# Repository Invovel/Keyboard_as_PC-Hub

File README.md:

# Keyboard as PC Hub

**Desktop Control Hub · R3.1：Core＋可选下置Power Dock＋低功耗MAG附件。**

Core背部PC-C是唯一电脑上行，单线从电脑允许的VBUS预算取电，目标为不依赖Dock即可使用主体与键盘。Hub硬件转发USB外设数据，ESP32负责圆屏、旋钮、四键、音频和HID；Hub启动不应依赖ESP32固件。单线功耗、Hub配置与故障独立性尚未通过整机验证。

[最新交接基准](docs/R3_1_CODEX_HANDOFF.md) · [差异与决策台账](docs/R3_1_DECISIONS.md) · [WP1/WP2工程评审](docs/R3_1_ENGINEERING_REVIEW.md) · [下一步入口](CODEX_START.md)

[补充讨论采用/放弃清单](docs/R3_1_SUPPLEMENT.md)：保留五键与104mm前部横条，补强Hub启动和Slider验证，早期双向供电/竖条/第二上行不混入当前设计。

**新增设计决定：[最右侧 ISO／DEBUG USB-A](docs/iso-debug-r3-1.md)。** PC-C候选中心移至X≈+64，ISO口X≈+91；由P6经独立USB2双下游Hub保留CTRL并增设隔离调试链路。首版采用隔离电源、集成限流/短路/防反灌保护、数据ESD和本地故障指示；精确计量留作后续选装。[候选材料表](hardware/electronics/iso-debug-candidate-bom.csv)不等于采购或保护能力认证。

[原理图摆位表](docs/iso-debug-schematic-placement-r3-1.md) · [A3摆位视图](design/drawings/iso-debug-schematic-placement-r3-1.svg) · [首版功能连接参考](design/drawings/iso-debug-minimal-schematic-r3-1.svg) · [Anatomy结构视图](design/visualization/iso-debug-anatomy.html) · [预览图](design/visualization/iso-debug-anatomy-preview.png)。当前仅确定原理图页内位置，未画导线或PCB；现有KiCad主工程尚未写入该页。

## 当前结构与接口

| 部位 | R3.1分工 |
| --- | --- |
| Core背部 | A1、A2、PC-C、最右侧ISO／DEBUG USB-A；PC-C唯一电脑上行，无Core POWER输入 |
| Core左侧 | FAST-C，目标10Gbps下游；实际供电按预算，不预先承诺3A |
| KBD / CTRL | 可调Type-C键盘公头 / 内部ESP32 USB2 Full-Speed HID |
| Core底部 | P4 Dock DATA＋独立PWR/CTRL预留，封装与开孔未定 |
| 可选下置Dock | Rev B：扩展Hub、外部PD受电、保护降压、单向给Core供电；没有第二电脑上行 |
| 两端MAG | 低速、低功耗8触点；五键及前部唯一横向触控条，不传高速USB/全机电流 |

逻辑下游P1=A1、P2=A2、P3=FAST、P4=DOCK、P5=KBD、P6=USB2分支至原CTRL与新ISO／DEBUG；这是架构分配，不是芯片物理引脚。USB7206C仍为候选，尚未证明Core单线工作能力。旧A3迁为Dock数据链路，POWER IN移至Dock；旧100W/46W单体预算仅保留为历史。

| 尺寸 | 候选值，mm |
| --- | --- |
| Core / PCB | 228×76、5°，前20/后26.65；PCB216×64×1.6 |
| 短四键 | 四片镜像，外端X=±84，两端各留30固定壳面；键面高0.3 |
| 感应中心 | (±65,±18)，保持原位 |
| 环 / 屏 / AA | Ø60 / Ø44.32 / Ø38.16；单边可见边框1.8 |
| 五键 / 横条 | 112×76一字五键；前部横条104×22×8，目标有效长90～96 |
| 底部Dock研究区 | 48×18功能区；8板间距和20高Dock包络均未冻结 |

新增[左右马达预留与PCB布局](hardware/pcb/references/core-haptic-placement-r3-1.md)：2026-10-22锁定[iPhone 7 Plus Taptic Engine](docs/haptic-iphone-7-plus.md)，按用户给定含耳50×12.5×2.6 mm设计，每侧装配区改为15×54×6 mm、长边沿Y，两端顶面保持完整留白。接线采用六测试焊盘最外侧两点接独立触觉驱动；[本轮原生执行记录](hardware/pcb/references/haptic-7plus-native-update.md)与[10月19日历史板图/DRC](hardware/pcb/exports/core-r3-1-haptic-study/README.md)分开保存。新板尚未接网/布线，不能打样。

## 原HTML持续更新

[原单文件HTML](design/visualization/hairline-keyboard-hub.html) · [使用与截图](design/visualization/README.md)。下载后离线打开；悬停主体展开、点击固定/复位，右侧五键及横条磁吸拆分。可选Dock只在主体展开时显示研究包络；默认Core不装Dock。GitHub README仅显示静态图。

[底部接口与侧剖](design/drawings/dock-interface-r3-1.svg) · [R3.1机械说明](hardware/enclosure/dimensions-r3-1.md) · [端口选型表](hardware/electronics/dock-port-selection.csv)

[ISO口与右马达、后孔空间关系](design/drawings/iso-debug-rear-study-r3-1.svg)：这是候选二维研究，开孔仍未冻结。

## 实物进展与文件分类

已运行主体：圆屏、触控页面、触摸板、USB键鼠/媒体HID、四键、按压输入、编码器与提示音；[实测历史](docs/body-core-bringup.md)保留原文。Touchpad延迟本轮不改。新增[INMP441代码](docs/microphone-inmp441.md)只编译，默认关闭，未接实物。输入按压通过不代表屏幕Z轴机械机构已完成。

| 分类 | 入口 | 状态 |
| --- | --- | --- |
| 固件 | [firmware](firmware/README.md) | 保留已运行GPIO与整合代码，本轮不改动/烧录 |
| 展示与图纸 | [design](design/README.md) | 原HTML、R3.1俯视/底视/剖面示意 |
| 机械 | [hardware/enclosure](hardware/enclosure/README.md) | R3.1参数/草模，未实体编译与装配验证 |
| PCB | [hardware/pcb](hardware/pcb/README.md) | 新增指定工程的R3.1布局草案与马达预留；未接网/布线，DRC未通过；R3载板保留历史 |
| 接口与接线 | [hardware/electronics](hardware/electronics/README.md) | 新接口目标与既有实物分开记录 |
| 镜像与证据 | [releases](releases/README.md)、[tests](tests/README.md) | 保留原镜像、许可和真实日志 |

尚未完成电源/Hub/Dock电路、连接器冻结、ERC、USB合规、闭壳温升或制造放行。新增布局已运行DRC但未通过；完整原理图与电气连接仍待完成。不做第二上行、双向大电流、手机高压PD输出、读卡、电池或竖触控条。

[目录规则](docs/repository-layout.md) · [本轮检查](tests/design/r3-1-review.md) · [R3历史尺寸](hardware/enclosure/dimensions-r3.md) · [旧单体供电方案](docs/desktop-power-dock.md) · [R2历史](hardware/enclosure/dimensions-r2.md)

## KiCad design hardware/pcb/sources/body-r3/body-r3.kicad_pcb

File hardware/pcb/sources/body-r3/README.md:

# R3 模块接口载板草稿

> 本工程保留为历史被动接口载板。本轮没有修改KiCad文件；R3.1原生Core与Dock电气仍待设计，见[最新审查](../../../../docs/R3_1_ENGINEERING_REVIEW.md)。下文100W单体供电及旧生成器说明不代表当前Core结构；不要运行旧生成器覆盖新版参数/图纸，KiCad后续修改须通过Konnect。

这是基于当前已运行固件 GPIO 与模块拓扑生成的 **KiCad 接口原理图 + PCB 布局草稿**。不是 Keychron PCB 的复刻，也不是制造放行板。

按[桌面供电底座定位](../../../../docs/desktop-power-dock.md)，本板是控制载板。新增100W等级PD输入、5V分路供电与USB7206C Hub需要单独子板，**本板J9仍只接5V**；更新产品定位没有实现这些电源电路。

- [body-r3.kicad_pro](body-r3.kicad_pro)：项目入口。
- [body-r3.kicad_sch](body-r3.kicad_sch)：内嵌连接器符号的原理图，11 个逻辑接口。
- [body-r3.kicad_pcb](body-r3.kicad_pcb)：216×64×1.6 mm 板框、34 个网络（包含空网络编号 0）、15 个封装（含安装孔）。**没有走线与铺铜**。
- [generate.py](generate.py)：已停用的旧入口，返回非零且不写文件；[原生成源文本](generate-r3-legacy.py.txt)只供历史阅读。新机械/参数用[update_r3_1.py](../../../enclosure/tools/update_r3_1.py)，后续KiCad变更经Konnect。
- [导出目录](../../exports/body-r3-review/README.md)：接口表、草稿 BOM、布局 SVG、未决事项。

## 可以从现有连接推导什么

屏幕 QSPI、触控 I²C、四键、按压、编码器 A/B、功放 I²S 与新增麦克风 I²S1 的逻辑网络已经明确，因而可以画出模块接口和连接关系。现有 ESP32-S3 开发板的精确型号、针脚排布、安装孔及屏幕背板/FPC 封装未测量，因此 J1/J2 使用**新定义的线束接口**，不假设某块开发板能直接插到这里。

J3/J4 等引脚号也是本载板新定义的线束顺序，不是宣称现有屏幕插座顺序。实际接线必须按模块丝印制作转接线，屏幕排线没有被替换成猜测的 FPC 封装。

## GPIO 基准与歧义处理

当前运行源码和双向日志支持编码器 A=1、B=2、①键=42。用户曾描述把 B 接到 42 后恢复，但当时没有改固件；因此这条口头描述不能直接冻结为 PCB 的 B=42，否则与①键冲突。本草稿以运行源码为基准保留独立网络，实物最终复核前不下单。

## 供电、USB 与磁吸边界

- 本板假设 5V_BODY 和 3V3 来自外部现有模块；没有集成稳压器、反灌保护或 PD。
- J9 是逻辑电源入口，不是 USB-C/PD 端口。现有 USB HID 继续走开发板原生 USB 口；本草稿没有路由 GPIO19/20、高速 USB 或 Hub。
- J10/J11 是左右磁吸转接的焊盘候选。磁吸附件为 DNP，5V_MAG_PROTECTED、3V3_MAG_ISOLATED、MAG_SDA/SCL 等网络未与主体电源/触控总线直连。需要后续限流、热插拔隔离、检测及连接器选型。
- 接点在主板顶面，距外壳端面约 8 mm；需独立 90° 转接小板/柔性连接到端面，不能把平面焊盘当作已完成侧向 pogo 结构。
- 100 nF 及 100 kΩ 等麦克风外围由现成模块承担或后续小板补齐；本次模块载板没有实现裸 INMP441 芯片电路。

## 检查结果

已由 `kiutils 1.4.8` 解析读取 PCB 和原理图，确认网络与接口文件可读；没有安装 KiCad，因此**没有运行 KiCad ERC、DRC，也未确认在 GUI 中打开的效果**。没有 Gerber、贴片坐标或生产就绪声明。

下一步是冻结真实模块封装及主控方案，确定电源/Hub/触点保护，然后布线与 DRC；不能从连接日志自动推断器件机械尺寸或高速电气设计。

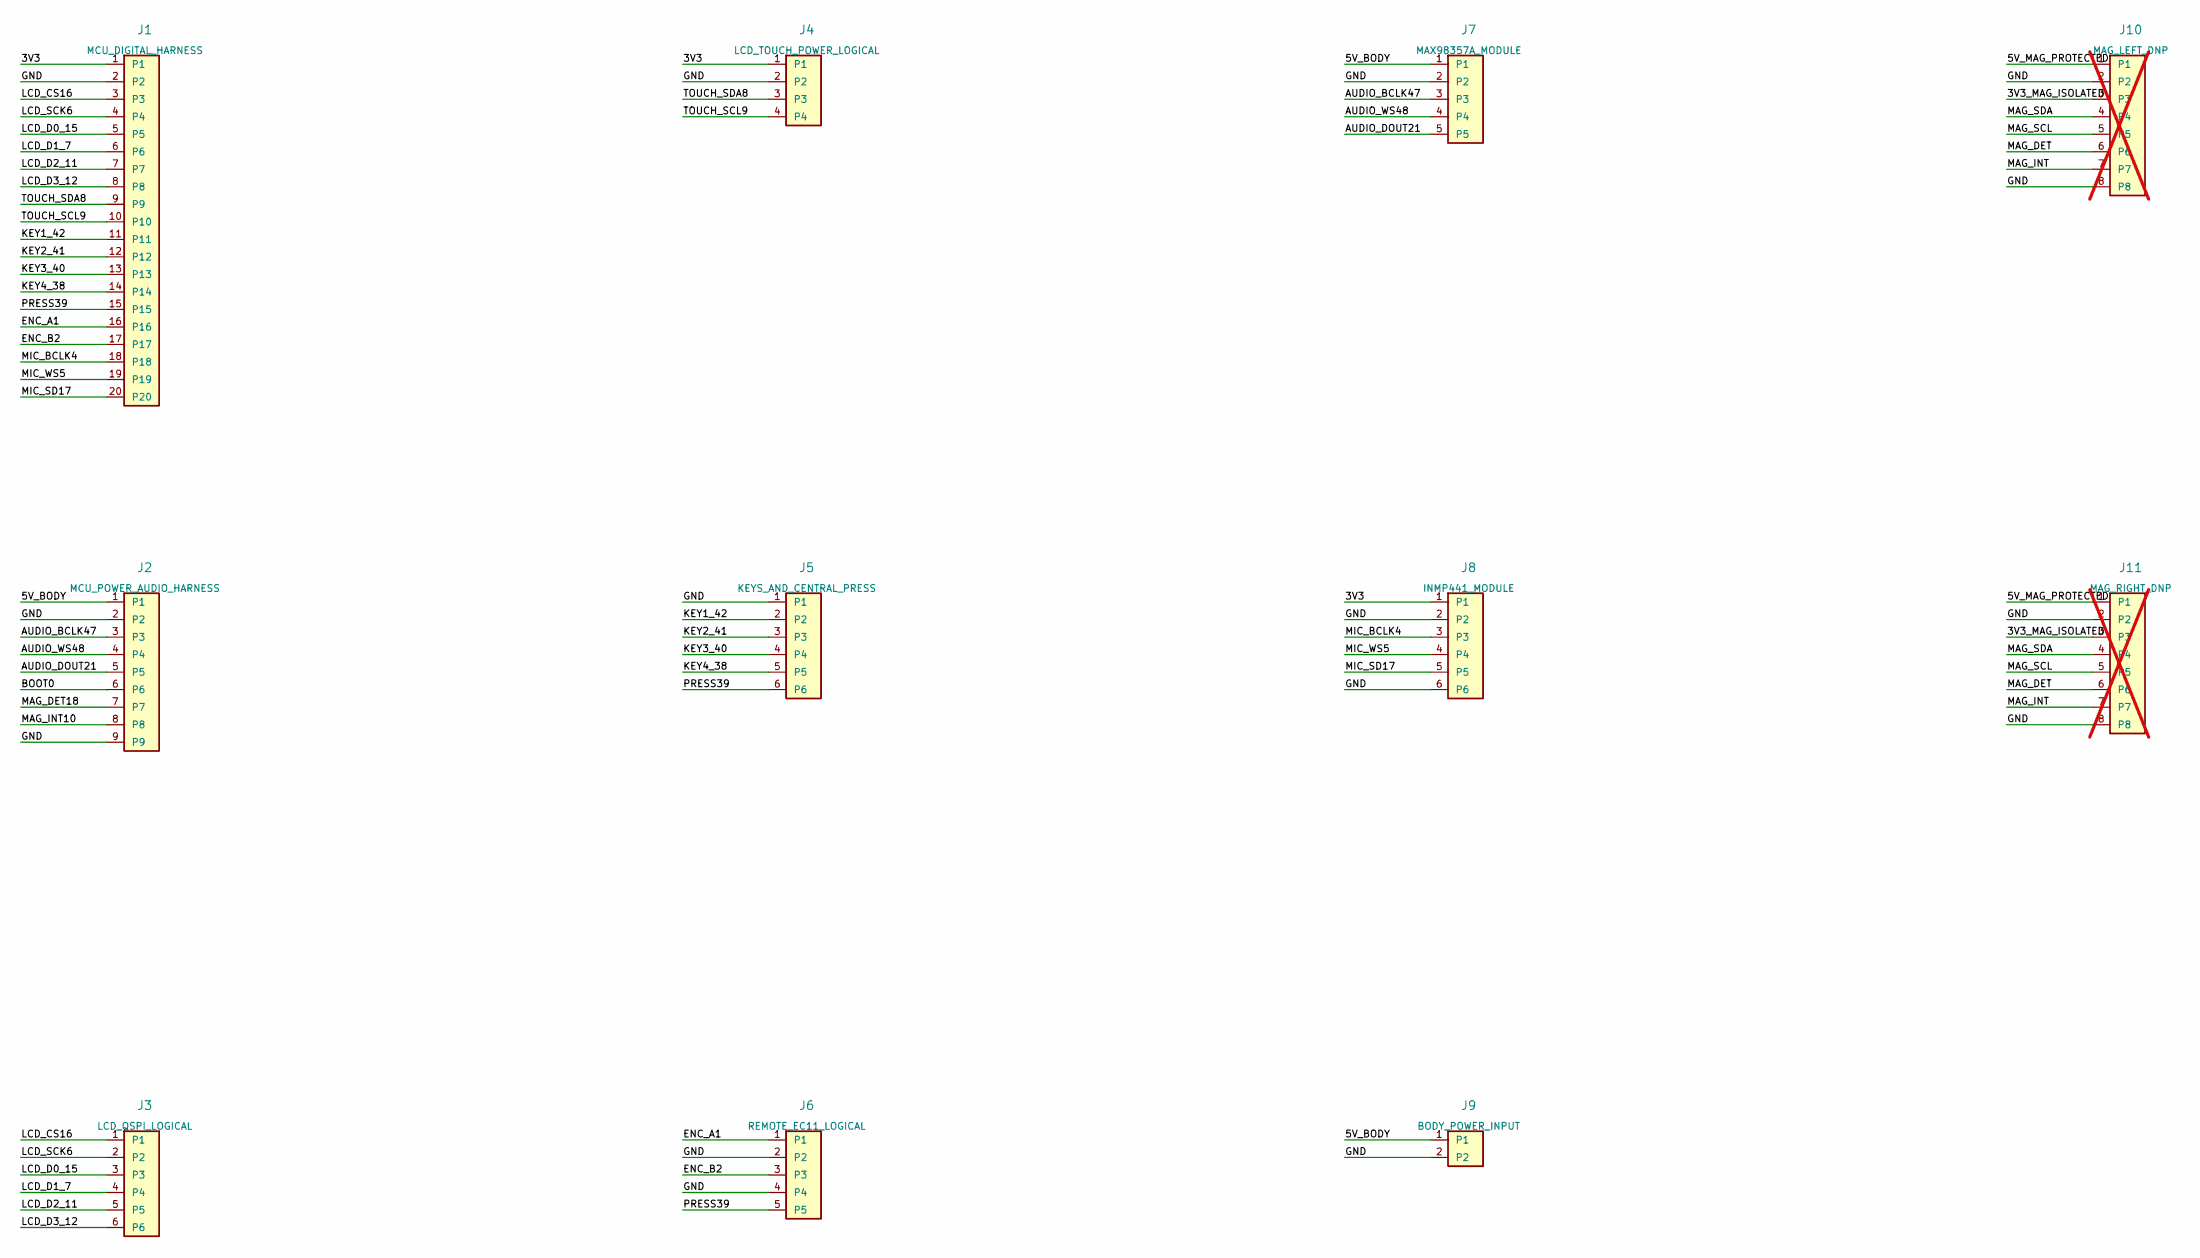
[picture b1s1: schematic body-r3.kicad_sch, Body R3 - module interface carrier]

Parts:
J1: MCU_DIGITAL_HARNESS
J2: MCU_POWER_AUDIO_HARNESS
J3: LCD_QSPI_LOGICAL
J4: LCD_TOUCH_POWER_LOGICAL
J5: KEYS_AND_CENTRAL_PRESS
J6: REMOTE_EC11_LOGICAL
J7: MAX98357A_MODULE
J8: INMP441_MODULE
J9: BODY_POWER_INPUT
J10: MAG_LEFT_DNP; not fitted
J11: MAG_RIGHT_DNP; not fitted

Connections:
3V3: J1.1, J4.1, J8.1
3V3_MAG_ISOLATED: J10.3, J11.3
5V_BODY: J2.1, J7.1, J9.1
5V_MAG_PROTECTED: J10.1, J11.1
AUDIO_BCLK47: J2.3, J7.3
AUDIO_DOUT21: J2.5, J7.5
AUDIO_WS48: J2.4, J7.4
BOOT0: J2.6
ENC_A1: J1.16, J6.1
ENC_B2: J1.17, J6.3
GND: J1.2, J2.2, J2.9, J4.2, J5.1, J6.2, J6.4, J7.2, J8.2, J8.6, J9.2, J10.2, J10.8, J11.2, J11.8
KEY1_42: J1.11, J5.2
KEY2_41: J1.12, J5.3
KEY3_40: J1.13, J5.4
KEY4_38: J1.14, J5.5
LCD_CS16: J1.3, J3.1
LCD_D0_15: J1.5, J3.3
LCD_D1_7: J1.6, J3.4
LCD_D2_11: J1.7, J3.5
LCD_D3_12: J1.8, J3.6
LCD_SCK6: J1.4, J3.2
MAG_DET: J10.6, J11.6
MAG_DET18: J2.7
MAG_INT: J10.7, J11.7
MAG_INT10: J2.8
MAG_SCL: J10.5, J11.5
MAG_SDA: J10.4, J11.4
MIC_BCLK4: J1.18, J8.3
MIC_SD17: J1.20, J8.5
MIC_WS5: J1.19, J8.4
PRESS39: J1.15, J5.6, J6.5
TOUCH_SCL9: J1.10, J4.4
TOUCH_SDA8: J1.9, J4.3

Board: 2 copper layers, 15 parts (0 on the bottom side), 30 nets, no tracks yet.

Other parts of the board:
H1, H2, H3, H4: M2_mount

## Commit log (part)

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2026-03-04 初始提交：STM32键盘Hub工程完整代码框架
